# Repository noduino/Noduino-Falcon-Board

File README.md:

Noduino Falcon Board
=======================================

[*Noduino Falcon Board - Complete Falcon board (FALCON V1.2)*](https://www.noduino.org/)

[*Noduino Falcon Board - Complete Falcon board (FALCON V2.4)*](https://www.noduino.org/)

[*Noduino Falcon Board Bottom - Complete Falcon board*](https://www.noduino.org/)

Overview
-------------------
Noduino Falcon is an ESP8266 Quick Development board.

The pin map of all versions of Falcon Board:

* D0	GPIO3 (U0RX) / URX during flash programming
* D1	GPIO1 (U0TX) / SPI CS1
* D2	GPIO2 (U1TX) / UTX during flash programming
* D3	GPIO15 (HSPI CS)
* D4	GPIO13 (HSPI MOSI)
* D5	GPIO12 (HSPI MISO)
* D6	GPIO14 (HSPI CLK)
* D7	GPIO16

* D8	GPIO4
* D9	GPIO5
* D10	GPIO0  (SPI CS2)
* D11	GPIO8 (SD D1 / SPI MOSI)
* D12	GPIO7 (SD D0 / SPI MISO)
* D13	GPIO6 (SD CLK / SPI CLK)

* A0	TOUT  Analog In

Repository Contents
-------------------
* V1.2/ - All Eagle design files (.brd, .sch) and Gerber files of Falcon version 1.4 (FT232RL USB to UART chip)
* V2.1/ - All Eagle desgin files (.brd, .sch) and Gerber files of Falcon version 2.1 (CP2102 USB to UART chip, 0402 cap and resistor)
* V2.2/ - All Eagle desgin files (.brd, .sch) and Gerber files of Falcon version 2.2 (CP2102 USB to UART chip, 0603 cap and resistor)
* V2.4/ - All Eagle desgin files (.brd, .sch) and Gerber files of Falcon version 2.4 (CP2102 USB to UART chip, WiFi module)

Product Versions
----------------
* [FALCON-100](http://www.noduino.org/) - FT232RL USB to UART chip.
* [FALCON-200](http://www.noduino.org/) - CP2102 USB to UART chip.
* [FALCON-300](http://www.noduino.org/) - CP2102 USB2UART chip, WiFi Module.

License Information
-------------------
The hardware is released under [Creative Commons ShareAlike 4.0 International](https://creativecommons.org/licenses/by-sa/4.0/).

Distributed as-is; no warranty is given.

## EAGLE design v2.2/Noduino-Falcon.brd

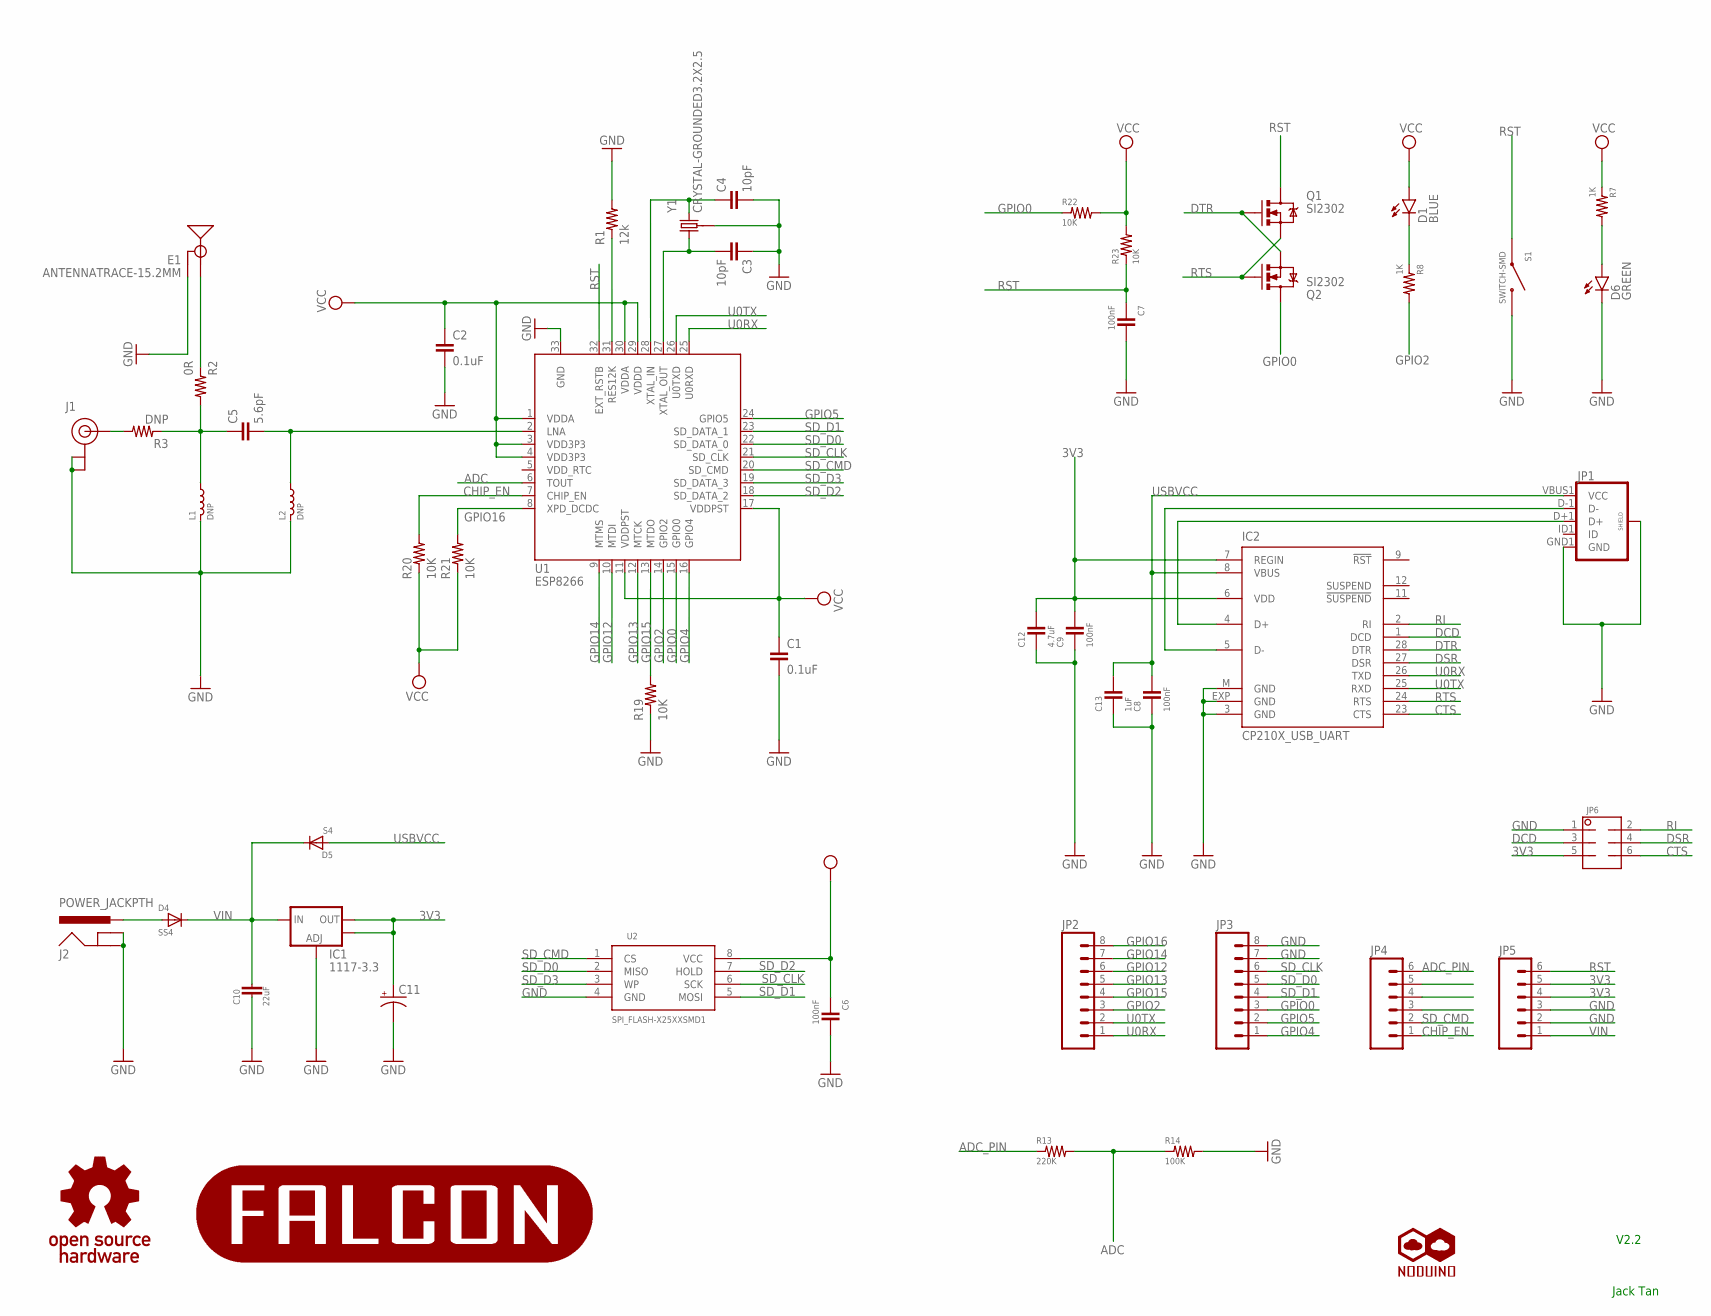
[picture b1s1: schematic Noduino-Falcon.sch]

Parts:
C1, C2: 0.1uF; 0603-CAP
C3, C4: 10pF; 0603-CAP
C5: 5.6pF; 0603-CAP
C6, C7, C8, C9: 100nF; 0603-CAP
C10: 22uF; C1206
C11: CAP_POL3528; EIA3528
C12: 4.7uF; 0603-CAP
C13: 1uF; 0603-CAP
D1: BLUE; LED-0603
D4: SS4; SMB-DIODE
D5: S4; SOD-323
D6: GREEN; LED-0603
E1: ANTENNATRACE-15.2MM; TRACE_ANTENNA_2.4GHZ_15.2MM
IC1: 1117-3.3; SOT223
IC2: CP210X_USB_UART; MLP28
J1: U.FL
J2: POWER_JACKPTH; POWER_JACK_PTH
JP1: USB_MICROB_PLUGCONN-11752; USB-B-MICRO-SMD_V03
JP2, JP3: M081X08; 1X08
JP4, JP5: M06SIP; 1X06
JP6: M02X3; 2X3
L1, L2: DNP; 0402-IND
Q1, Q2: SI2302; SOT23-3
R1: 12k; 0603-RES
R2: 0R; 0603-RES
R3: DNP; 0402-RES
R7, R8: 1K; 0603-RES
R13: 220K; 0603-RES
R14: 100K; 0603-RES
R19, R20, R21, R22, R23: 10K; 0603-RES
S1: SWITCH-SMD; TACTILE-SWITCH-1101NE
U1: ESP8266; QFN-32
U2: SPI_FLASH-X25XXSMD1; SO08-EIAJ
U$1: NODUINO-LOGO-ALL; NODUINO-ALL-1
U$2: NODUINO-FALCON
U$3: OPEN_HARDWARE_LOGO
Y1: CRYSTAL-GROUNDED3.2X2.5; CRYSTAL-SMD-3.2X2.5

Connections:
3V3: C1.1, C2.1, C6.1, C9.2, C11.A (+), C12.2, D1.A, IC1.2 (OUT), IC1.4 (OUT), IC2.6 (VDD), IC2.7 (REGIN), JP5.4, JP5.5, JP6.5, R7.1, R20.1, R21.1, R22.2, R23.2, U1.1 (VDDA), U1.3 (VDD3P3), U1.4 (VDD3P3), U1.11 (VDDPST), U1.17 (VDDPST), U1.29 (VDDD), U1.30 (VDDA), U2.8 (VCC)
ADC: R13.2, R14.1, U1.6 (TOUT)
ADC_PIN: JP4.6, R13.1
CHIP_EN: JP4.1, R20.2, U1.7 (CHIP_EN)
CTS: IC2.23 (CTS), JP6.6
DCD: IC2.1 (DCD), JP6.3
DSR: IC2.27 (DSR), JP6.4
DTR: IC2.28 (DTR), Q1.1 (G), Q2.2 (S)
GND: C1.2, C2.2, C3.1, C4.2, C6.2, C7.2, C8.1, C9.1, C10.2, C11.C (-), C12.1, C13.1, D6.C, E1.GND, IC1.1 (ADJ), IC2.3 (GND), IC2.EXP (GND), IC2.M (GND), J1.P$1 (GND), J1.P$2 (GND), J2.GND, J2.GNDBREAK, JP1.GND1 (GND), JP1.SHIELD1 (SHIELD), JP1.SHIELD2 (SHIELD), JP1.SHIELD3 (SHIELD), JP3.7, JP3.8, JP5.2, JP5.3, JP6.1, L1.1 (X1), L2.1 (X1), R1.2, R14.2, R19.1, S1.P$1 (1), U1.33 (GND), U2.4 (GND), Y1.2 (GND), Y1.4 (GND)
GPIO0: JP3.3, Q2.3 (D), R22.1, U1.15 (GPIO0)
GPIO2: JP2.3, R8.2, U1.14 (GPIO2)
GPIO4: JP3.1, U1.16 (GPIO4)
GPIO5: JP3.2, U1.24 (GPIO5)
GPIO12: JP2.6, U1.10 (MTDI)
GPIO13: JP2.5, U1.12 (MTCK)
GPIO14: JP2.7, U1.9 (MTMS)
GPIO15: JP2.4, R19.2, U1.13 (MTDO)
GPIO16: JP2.8, R21.2, U1.8 (XPD_DCDC)
LNA: C5.2, L2.2 (X2), U1.2 (LNA)
unnamed: D1.C, R8.1
unnamed: C4.1, U1.28 (XTAL_IN), Y1.3 (2)
unnamed: C3.2, U1.27 (XTAL_OUT), Y1.1
unnamed: IC2.4 (D+), JP1.D+1 (D+)
unnamed: E1.ANT (SIGNAL), R2.1
unnamed: IC2.5 (D-), JP1.D-1 (D-)
unnamed: D6.A, R7.2
unnamed: D4.A, J2.PWR
unnamed: R1.1, U1.31 (RES12K)
unnamed: J1.P$3 (SIGNAL), R3.2
unnamed: C5.1, L1.2 (X2), R2.2, R3.1
RI: IC2.2 (RI), JP6.2
RST: C7.1, JP5.6, Q1.3 (D), R23.1, S1.P$2 (2), U1.32 (EXT_RSTB)
RTS: IC2.24 (RTS), Q1.2 (S), Q2.1 (G)
SD_CLK: JP3.6, U1.21 (SD_CLK), U2.6 (SCK)
SD_CMD: JP4.2, U1.20 (SD_CMD), U2.1 (CS)
SD_D0: JP3.5, U1.22 (SD_DATA_0), U2.2 (MISO)
SD_D1: JP3.4, U1.23 (SD_DATA_1), U2.5 (MOSI)
SD_D2: U1.18 (SD_DATA_2), U2.7 (HOLD)
SD_D3: U1.19 (SD_DATA_3), U2.3 (WP)
U0RX: IC2.26 (TXD), JP2.1, U1.25 (U0RXD)
U0TX: IC2.25 (RXD), JP2.2, U1.26 (U0TXD)
USBVCC: C8.2, C13.2, D5.2 (A), IC2.8 (VBUS), JP1.VBUS1 (VCC)
VIN: C10.1, D4.C, D5.1 (C), IC1.3 (IN), JP5.1

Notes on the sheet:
Jack Tan
V2.2

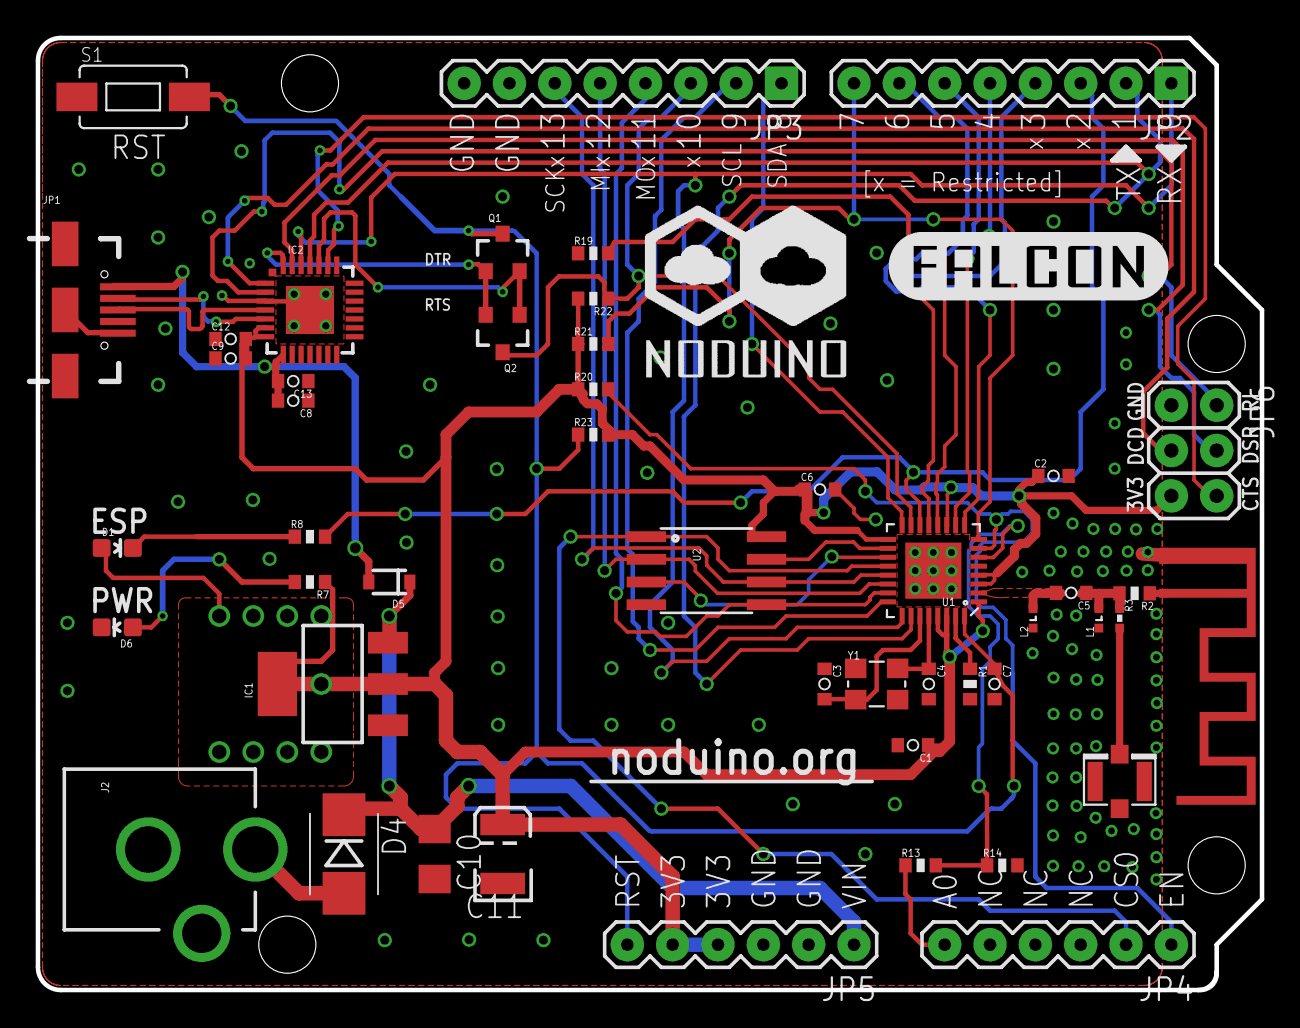
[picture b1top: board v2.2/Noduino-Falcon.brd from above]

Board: 2 copper layers, 68.6 x 53.3 mm, 51 parts (1 on the bottom side), 43 nets.

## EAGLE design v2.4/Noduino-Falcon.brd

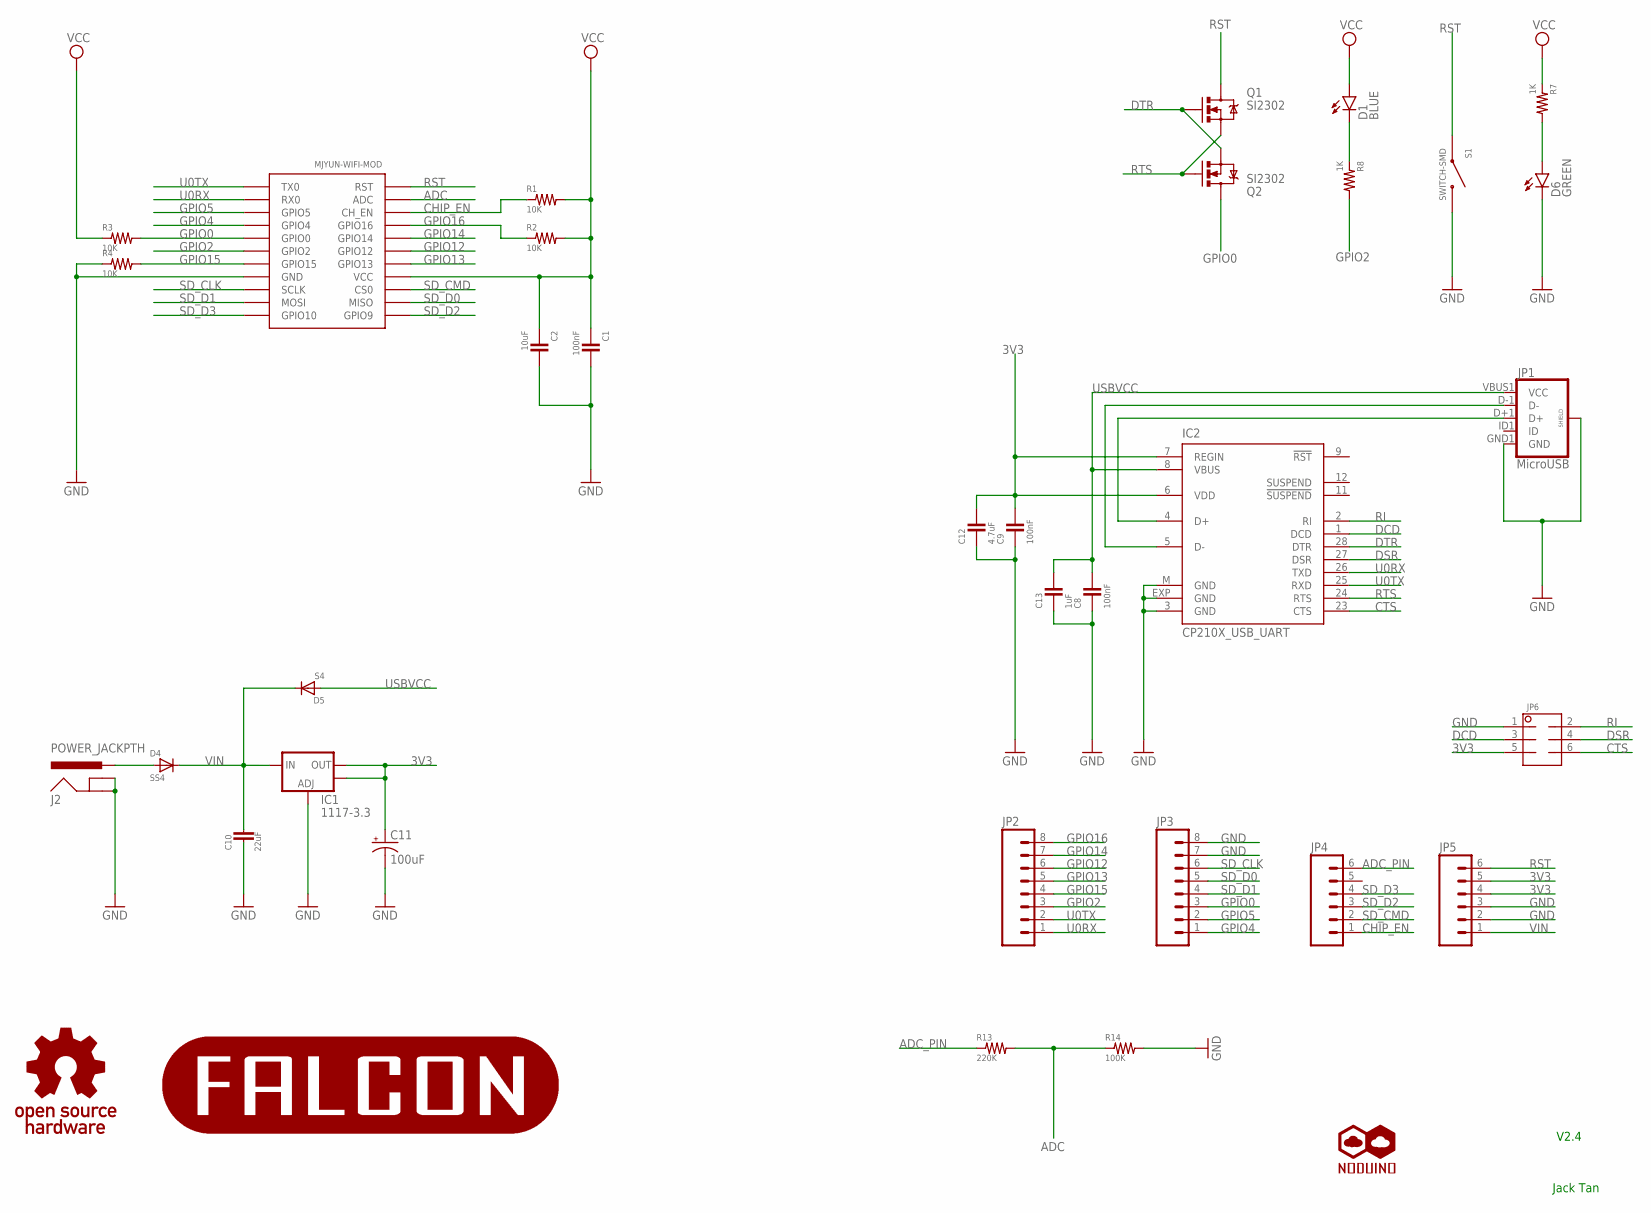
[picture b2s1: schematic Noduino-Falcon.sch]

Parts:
C1, C8, C9: 100nF; 0603-CAP
C2: 10uF; 0603-CAP
C10: 22uF; C1206
C11: 100uF; EIA3528
C12: 4.7uF; 0603-CAP
C13: 1uF; 0603-CAP
D1: BLUE; LED-0603
D4: SS4; SMB-DIODE
D5: S4; SOD-323
D6: GREEN; LED-0603
IC1: 1117-3.3; SOT223
IC2: CP210X_USB_UART; MLP28
J2: POWER_JACKPTH; POWER_JACK_PTH
JP1: MicroUSB; USB-B-MICRO-SMD_V03
JP2, JP3: M081X08; 1X08
JP4, JP5: M06SIP; 1X06
JP6: M02X3; 2X3
MJYUN-WIFI-MOD: ESP-1212F-DIP-SMD; ESP-12F-DIP
Q1, Q2: SI2302; SOT23-3
R1, R2, R3, R4: 10K; 0603-RES
R7, R8: 1K; 0603-RES
R13: 220K; 0603-RES
R14: 100K; 0603-RES
S1: SWITCH-SMD; TACTILE-SWITCH-1101NE
U$1: NODUINO-LOGO-ALL; NODUINO-ALL-1
U$2: NODUINO-FALCON
U$3: OPEN_HARDWARE_LOGO

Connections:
3V3: C1.1, C2.1, C9.2, C11.A (+), C12.2, D1.A, IC1.2 (OUT), IC1.4 (OUT), IC2.6 (VDD), IC2.7 (REGIN), JP5.4, JP5.5, JP6.5, MJYUN-WIFI-MOD.P$8 (VCC), MJYUN-WIFI-MOD.P$108 (VCC), R1.2, R2.2, R3.1, R7.1
ADC: MJYUN-WIFI-MOD.P$2 (ADC), MJYUN-WIFI-MOD.P$102 (ADC), R13.2, R14.1
ADC_PIN: JP4.6, R13.1
CHIP_EN: JP4.1, MJYUN-WIFI-MOD.P$3 (CH_EN), MJYUN-WIFI-MOD.P$103 (CH_EN), R1.1
CTS: IC2.23 (CTS), JP6.6
DCD: IC2.1 (DCD), JP6.3
DSR: IC2.27 (DSR), JP6.4
DTR: IC2.28 (DTR), Q1.1 (G), Q2.2 (S)
GND: C1.2, C2.2, C8.1, C9.1, C10.2, C11.C (-), C12.1, C13.1, D6.C, IC1.1 (ADJ), IC2.3 (GND), IC2.EXP (GND), IC2.M (GND), J2.GND, J2.GNDBREAK, JP1.GND1 (GND), JP1.SHIELD1 (SHIELD), JP1.SHIELD2 (SHIELD), JP1.SHIELD3 (SHIELD), JP3.7, JP3.8, JP5.2, JP5.3, JP6.1, MJYUN-WIFI-MOD.P$15 (GND), MJYUN-WIFI-MOD.P$115 (GND), R4.1, R14.2, S1.P$1 (1)
GPIO0: JP3.3, MJYUN-WIFI-MOD.P$18 (GPIO0), MJYUN-WIFI-MOD.P$118 (GPIO0), Q2.3 (D), R3.2
GPIO2: JP2.3, MJYUN-WIFI-MOD.P$17 (GPIO2), MJYUN-WIFI-MOD.P$117 (GPIO2), R8.2
GPIO4: JP3.1, MJYUN-WIFI-MOD.P$19 (GPIO4), MJYUN-WIFI-MOD.P$119 (GPIO4)
GPIO5: JP3.2, MJYUN-WIFI-MOD.P$20 (GPIO5), MJYUN-WIFI-MOD.P$120 (GPIO5)
GPIO12: JP2.6, MJYUN-WIFI-MOD.P$6 (GPIO12), MJYUN-WIFI-MOD.P$106 (GPIO12)
GPIO13: JP2.5, MJYUN-WIFI-MOD.P$7 (GPIO13), MJYUN-WIFI-MOD.P$107 (GPIO13)
GPIO14: JP2.7, MJYUN-WIFI-MOD.P$5 (GPIO14), MJYUN-WIFI-MOD.P$105 (GPIO14)
GPIO15: JP2.4, MJYUN-WIFI-MOD.P$16 (GPIO15), MJYUN-WIFI-MOD.P$116 (GPIO15), R4.2
GPIO16: JP2.8, MJYUN-WIFI-MOD.P$4 (GPIO16), MJYUN-WIFI-MOD.P$104 (GPIO16), R2.1
unnamed: D1.C, R8.1
unnamed: IC2.4 (D+), JP1.D+1 (D+)
unnamed: IC2.5 (D-), JP1.D-1 (D-)
unnamed: D6.A, R7.2
unnamed: D4.A, J2.PWR
RI: IC2.2 (RI), JP6.2
RST: JP5.6, MJYUN-WIFI-MOD.P$1 (RST), MJYUN-WIFI-MOD.P$101 (RST), Q1.3 (D), S1.P$2 (2)
RTS: IC2.24 (RTS), Q1.2 (S), Q2.1 (G)
SD_CLK: JP3.6, MJYUN-WIFI-MOD.P$14 (SCLK)
SD_CMD: JP4.2, MJYUN-WIFI-MOD.P$9 (CS0)
SD_D0: JP3.5, MJYUN-WIFI-MOD.P$10 (MISO)
SD_D1: JP3.4, MJYUN-WIFI-MOD.P$13 (MOSI)
SD_D2: JP4.3, MJYUN-WIFI-MOD.P$11 (GPIO9)
SD_D3: JP4.4, MJYUN-WIFI-MOD.P$12 (GPIO10)
U0RX: IC2.26 (TXD), JP2.1, MJYUN-WIFI-MOD.P$21 (RX0), MJYUN-WIFI-MOD.P$121 (RX0)
U0TX: IC2.25 (RXD), JP2.2, MJYUN-WIFI-MOD.P$22 (TX0), MJYUN-WIFI-MOD.P$122 (TX0)
USBVCC: C8.2, C13.2, D5.2 (A), IC2.8 (VBUS), JP1.VBUS1 (VCC)
VIN: C10.1, D4.C, D5.1 (C), IC1.3 (IN), JP5.1

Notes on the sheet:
Jack Tan
V2.4

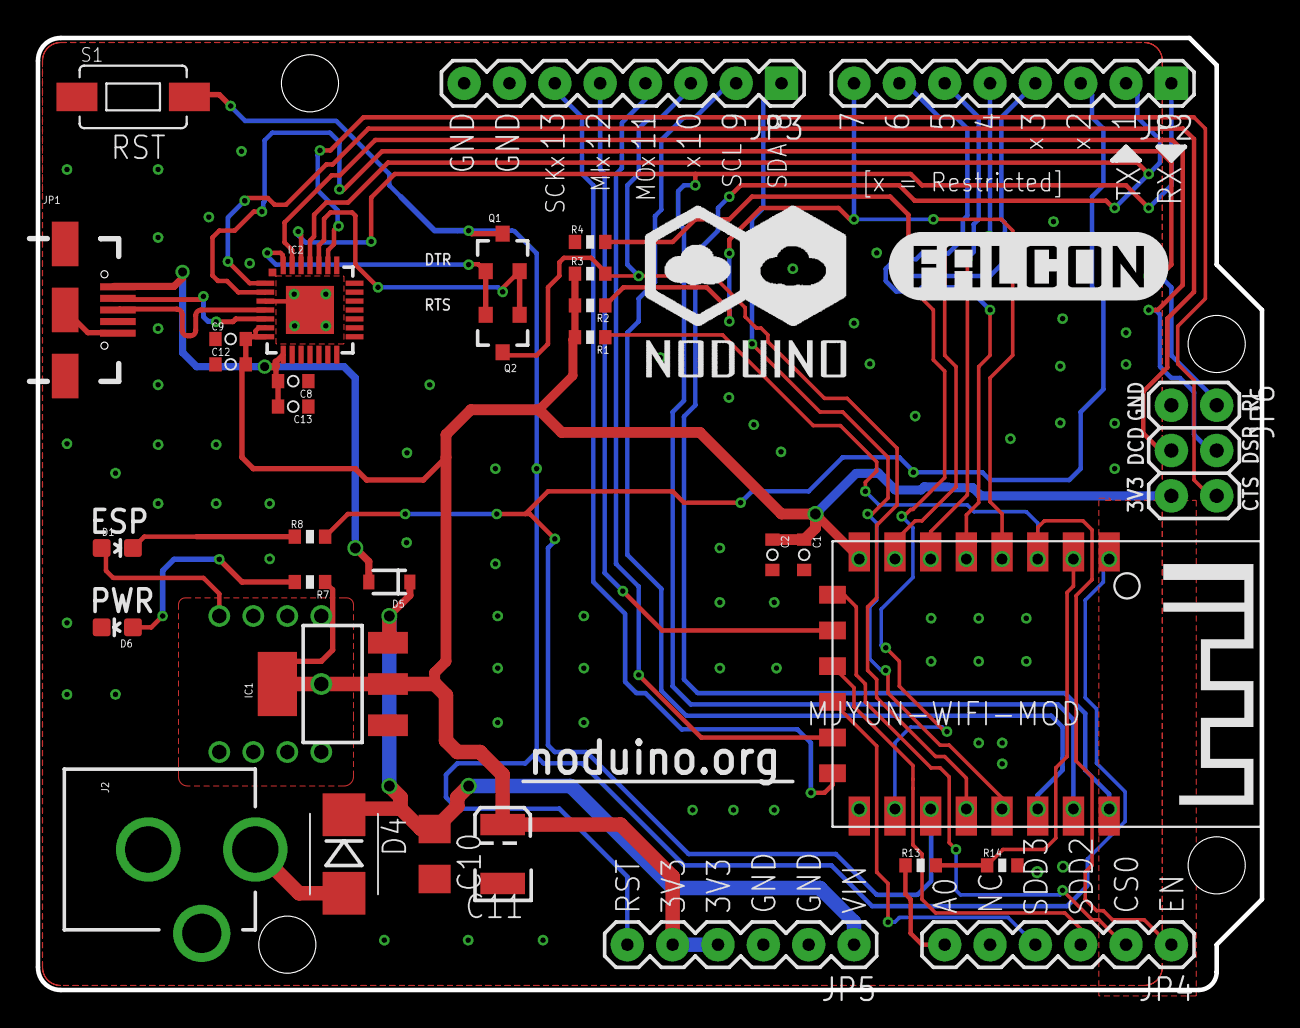
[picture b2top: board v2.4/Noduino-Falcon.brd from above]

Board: 2 copper layers, 68.6 x 53.3 mm, 36 parts (1 on the bottom side), 36 nets.

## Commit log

2016-02-01 add the readme and board picture
2016-02-01 add the url of the board picture in readme
2016-02-01 remove the useless message
2016-02-01 fixup the url of noduino.org
2016-02-01 rename the 'protoshield kit' to 'geek kit'
2016-02-01 add the Eagle design files (.brd, .sch) of v1.2
2016-02-01 add all gerber files of v1.2
2016-02-01 export the image of the design of v1.2
2016-02-01 add the Eagle design files (.brd, .sch) of v2.1
2016-02-01 export the images of the eagle design of the v2.1
2016-02-01 add the gerber files of v2.1
2016-07-25 update readme and a board picture of v2.4 version
2016-07-25 add the eagle design files and gerber file of v2.4
2016-08-01 add the eagle design files and gerber file of v2.2
2016-08-01 update the readme
    add the information of pin map of falcon board
2016-08-01 add the bottom image of falcon
